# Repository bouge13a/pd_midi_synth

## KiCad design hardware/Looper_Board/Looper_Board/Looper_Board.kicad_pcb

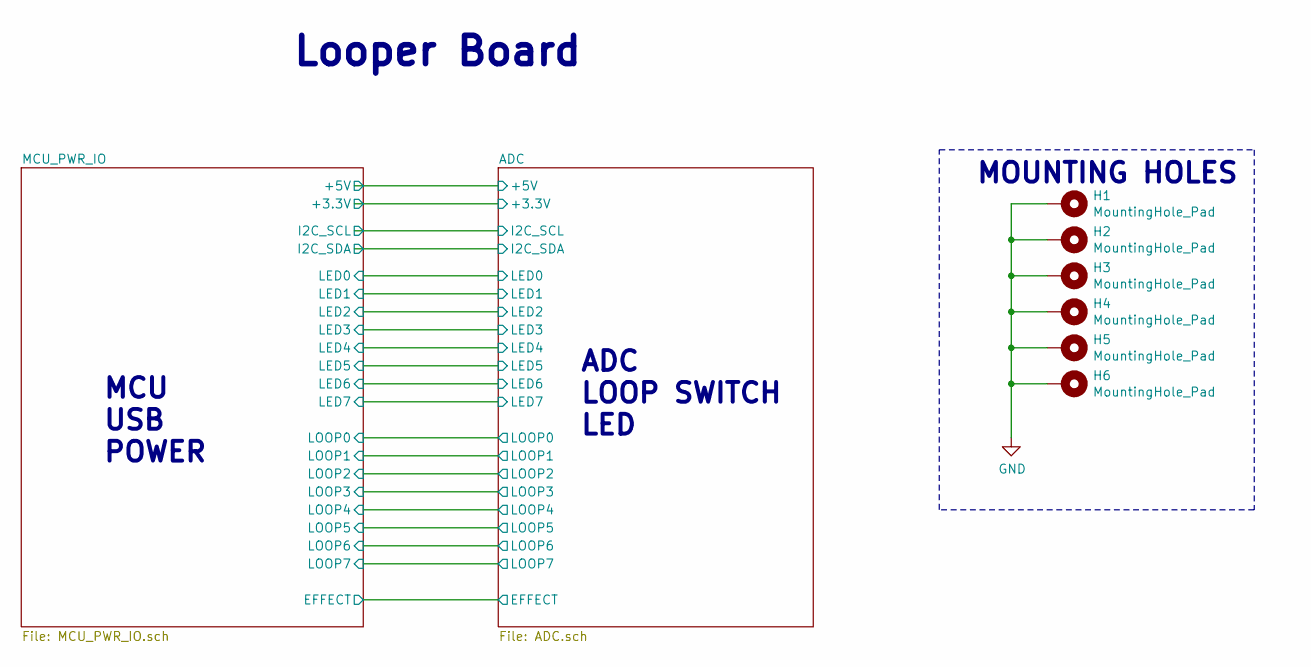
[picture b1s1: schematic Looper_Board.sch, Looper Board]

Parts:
H1, H2, H3, H4, H5, H6: MountingHole_Pad; MountingHole_3mm_Pad_Via

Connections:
GND: H1.1, H2.1, H3.1, H4.1, H5.1, H6.1; also elsewhere on the board

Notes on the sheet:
ADC LOOP SWITCH LED
MCU USB POWER
Looper Board
MOUNTING HOLES

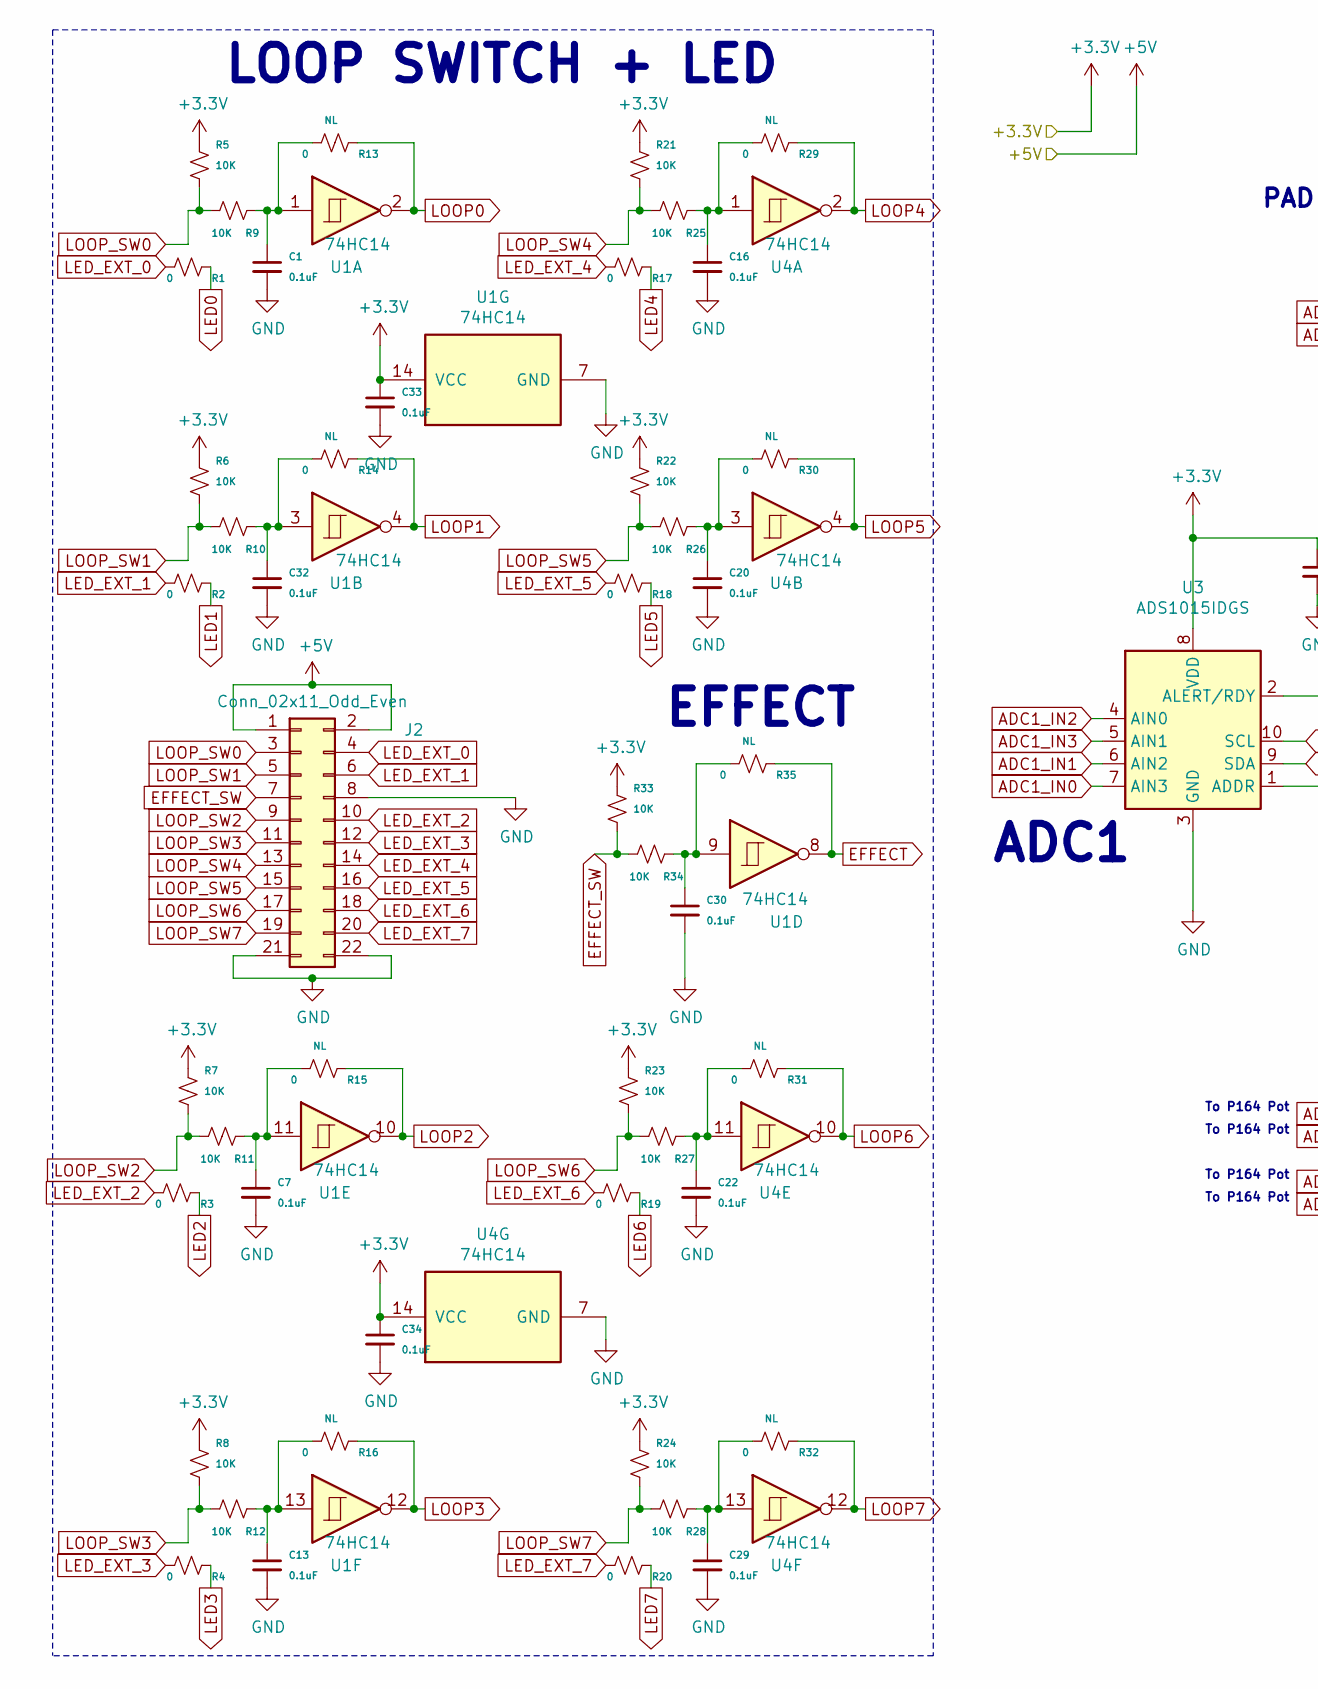
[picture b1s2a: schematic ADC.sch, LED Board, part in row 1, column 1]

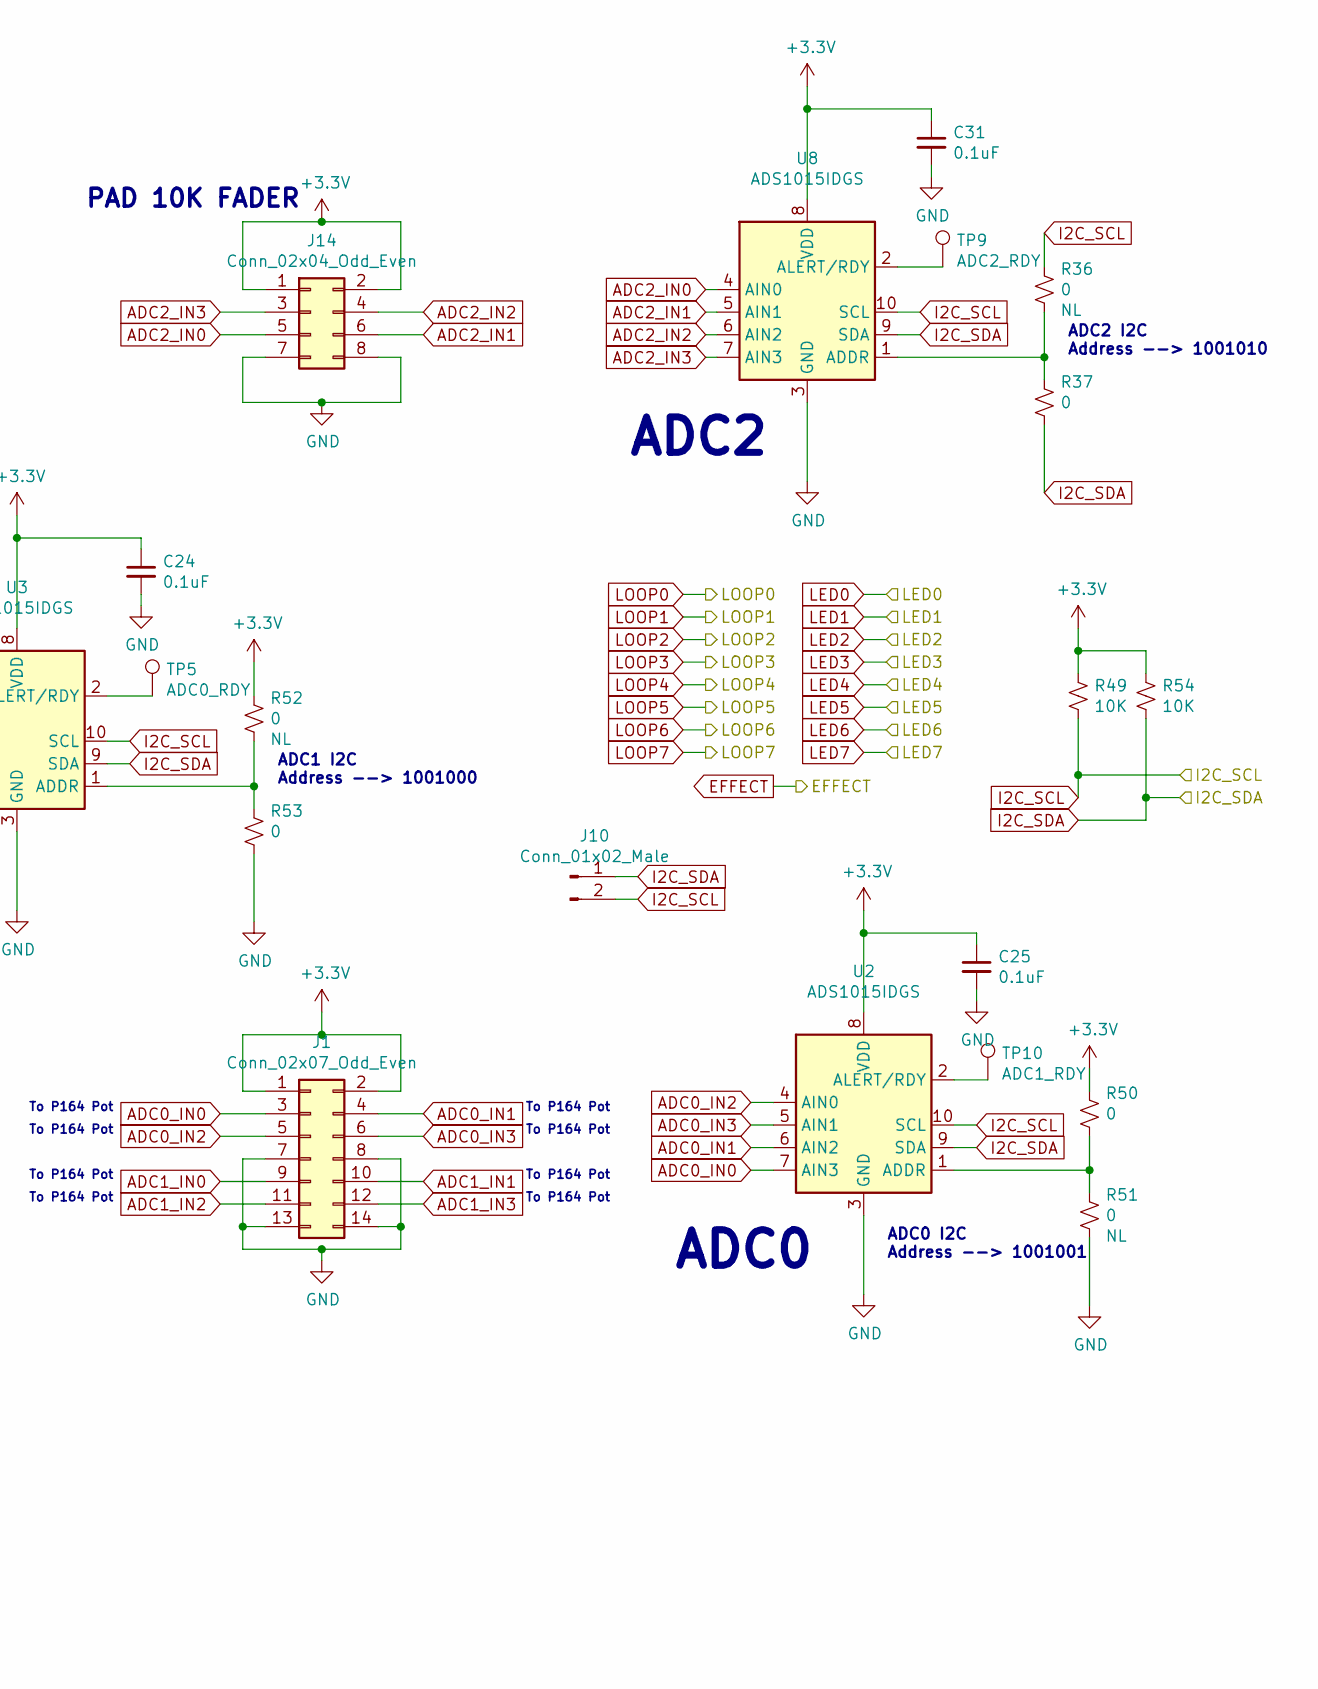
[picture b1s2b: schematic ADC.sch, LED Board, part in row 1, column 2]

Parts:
C1, C7, C13, C16, C20, C22, C24, C25, C29, C30, C31, C32, C33, C34: 0.1uF; C_0402_1005Metric_Pad0.74x0.62mm_HandSolder
J1: Conn_02x07_Odd_Even; PinHeader_2x07_P2.54mm_Horizontal
J2: Conn_02x11_Odd_Even; PinHeader_2x11_P2.54mm_Horizontal
J10: Conn_01x02_Male; PinHeader_1x02_P2.54mm_Vertical
J14: Conn_02x04_Odd_Even; PinHeader_2x04_P2.54mm_Horizontal
R1, R2, R3, R4, R13, R14, R15, R16, R17, R18, R19, R20, R29, R30, R31, R32, R35, R36, R37, R50, R51, R52, R53: 0; R_0402_1005Metric_Pad0.72x0.64mm_HandSolder
R5, R6, R7, R8, R9, R10, R11, R12, R21, R22, R23, R24, R25, R26, R27, R28, R33, R34, R49, R54: 10K; R_0402_1005Metric_Pad0.72x0.64mm_HandSolder
TP5: ADC0_RDY; TestPoint_Pad_D1.5mm
TP9: ADC2_RDY; TestPoint_Pad_D1.5mm
TP10: ADC1_RDY; TestPoint_Pad_D1.5mm
U1, U4: 74HC14; SOIC-14_3.9x8.7mm_P1.27mm
U2, U3, U8: ADS1015IDGS; VSSOP-10_3x3mm_P0.5mm

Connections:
+3V3: C24.1, C25.1, C31.1, C33.1, C34.1, J1.1, J1.2, J14.1, J14.2, R5.1, R6.1, R7.1, R8.1, R21.1, R22.1, R23.1, R24.1, R33.1, R49.1, R50.1, R52.1, R54.1, U1.14 (VCC), U2.8 (VDD), U3.8 (VDD), U4.14 (VCC), U8.8 (VDD); also elsewhere on the board
+5V: J2.1, J2.2; also elsewhere on the board
ADC0_IN0: J1.3, U2.7 (AIN3)
ADC0_IN1: J1.4, U2.6 (AIN2)
ADC0_IN2: J1.5, U2.4 (AIN0)
ADC0_IN3: J1.6, U2.5 (AIN1)
ADC1_IN0: J1.9, U3.7 (AIN3)
ADC1_IN1: J1.10, U3.6 (AIN2)
ADC1_IN2: J1.11, U3.4 (AIN0)
ADC1_IN3: J1.12, U3.5 (AIN1)
ADC2_IN0: J14.5, U8.4 (AIN0)
ADC2_IN1: J14.6, U8.5 (AIN1)
ADC2_IN2: J14.4, U8.6 (AIN2)
ADC2_IN3: J14.3, U8.7 (AIN3)
EFFECT: R35.1, U1.8; also elsewhere on the board
EFFECT_SW: J2.7, R33.2, R34.2
GND: C1.2, C7.2, C13.2, C16.2, C20.2, C22.2, C24.2, C25.2, C29.2, C30.2, C31.2, C32.2, C33.2, C34.2, J1.7, J1.8, J1.13, J1.14, J2.8, J2.21, J2.22, J14.7, J14.8, R51.2, R53.2, U1.7 (GND), U2.3 (GND), U3.3 (GND), U4.7 (GND), U8.3 (GND); also elsewhere on the board
I2C_SCL: J10.2, R36.1, R49.2, U2.10 (SCL), U3.10 (SCL), U8.10 (SCL); also elsewhere on the board
I2C_SDA: J10.1, R37.2, R54.2, U2.9 (SDA), U3.9 (SDA), U8.9 (SDA); also elsewhere on the board
LED0: R1.1; also elsewhere on the board
LED1: R2.1; also elsewhere on the board
LED2: R3.1; also elsewhere on the board
LED3: R4.1; also elsewhere on the board
LED4: R17.1; also elsewhere on the board
LED5: R18.1; also elsewhere on the board
LED6: R19.1; also elsewhere on the board
LED7: R20.1; also elsewhere on the board
LED_EXT_0: J2.4, R1.2
LED_EXT_1: J2.6, R2.2
LED_EXT_2: J2.10, R3.2
LED_EXT_3: J2.12, R4.2
LED_EXT_4: J2.14, R17.2
LED_EXT_5: J2.16, R18.2
LED_EXT_6: J2.18, R19.2
LED_EXT_7: J2.20, R20.2
LOOP0: R13.1, U1.2; also elsewhere on the board
LOOP1: R14.1, U1.4; also elsewhere on the board
LOOP2: R15.1, U1.10; also elsewhere on the board
LOOP3: R16.1, U1.12; also elsewhere on the board
LOOP4: R29.1, U4.2; also elsewhere on the board
LOOP5: R30.1, U4.4; also elsewhere on the board
LOOP6: R31.1, U4.10; also elsewhere on the board
LOOP7: R32.1, U4.12; also elsewhere on the board
LOOP_SW0: J2.3, R5.2, R9.2
LOOP_SW1: J2.5, R6.2, R10.2
LOOP_SW2: J2.9, R7.2, R11.2
LOOP_SW3: J2.11, R8.2, R12.2
LOOP_SW4: J2.13, R21.2, R25.2
LOOP_SW5: J2.15, R22.2, R26.2
LOOP_SW6: J2.17, R23.2, R27.2
LOOP_SW7: J2.19, R24.2, R28.2
unnamed: C1.1, R9.1, R13.2, U1.1
unnamed: C7.1, R11.1, R15.2, U1.11
unnamed: C13.1, R12.1, R16.2, U1.13
unnamed: C16.1, R25.1, R29.2, U4.1
unnamed: C20.1, R26.1, R30.2, U4.3
unnamed: C22.1, R27.1, R31.2, U4.11
unnamed: C29.1, R28.1, R32.2, U4.13
unnamed: C30.1, R34.1, R35.2, U1.9
unnamed: C32.1, R10.1, R14.2, U1.3
unnamed: R36.2, R37.1, U8.1 (ADDR)
unnamed: R50.2, R51.1, U2.1 (ADDR)
unnamed: R52.2, R53.1, U3.1 (ADDR)
unnamed: TP5.1, U3.2 (ALERT/RDY)
unnamed: TP9.1, U8.2 (ALERT/RDY)
unnamed: TP10.1, U2.2 (ALERT/RDY)

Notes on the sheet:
To P164 Pot
ADC0
ADC1
ADC1 I2C Address --> 1001000
ADC0 I2C Address --> 1001001
LOOP SWITCH + LED
EFFECT
ADC2
ADC2 I2C Address --> 1001010
PAD 10K FADER

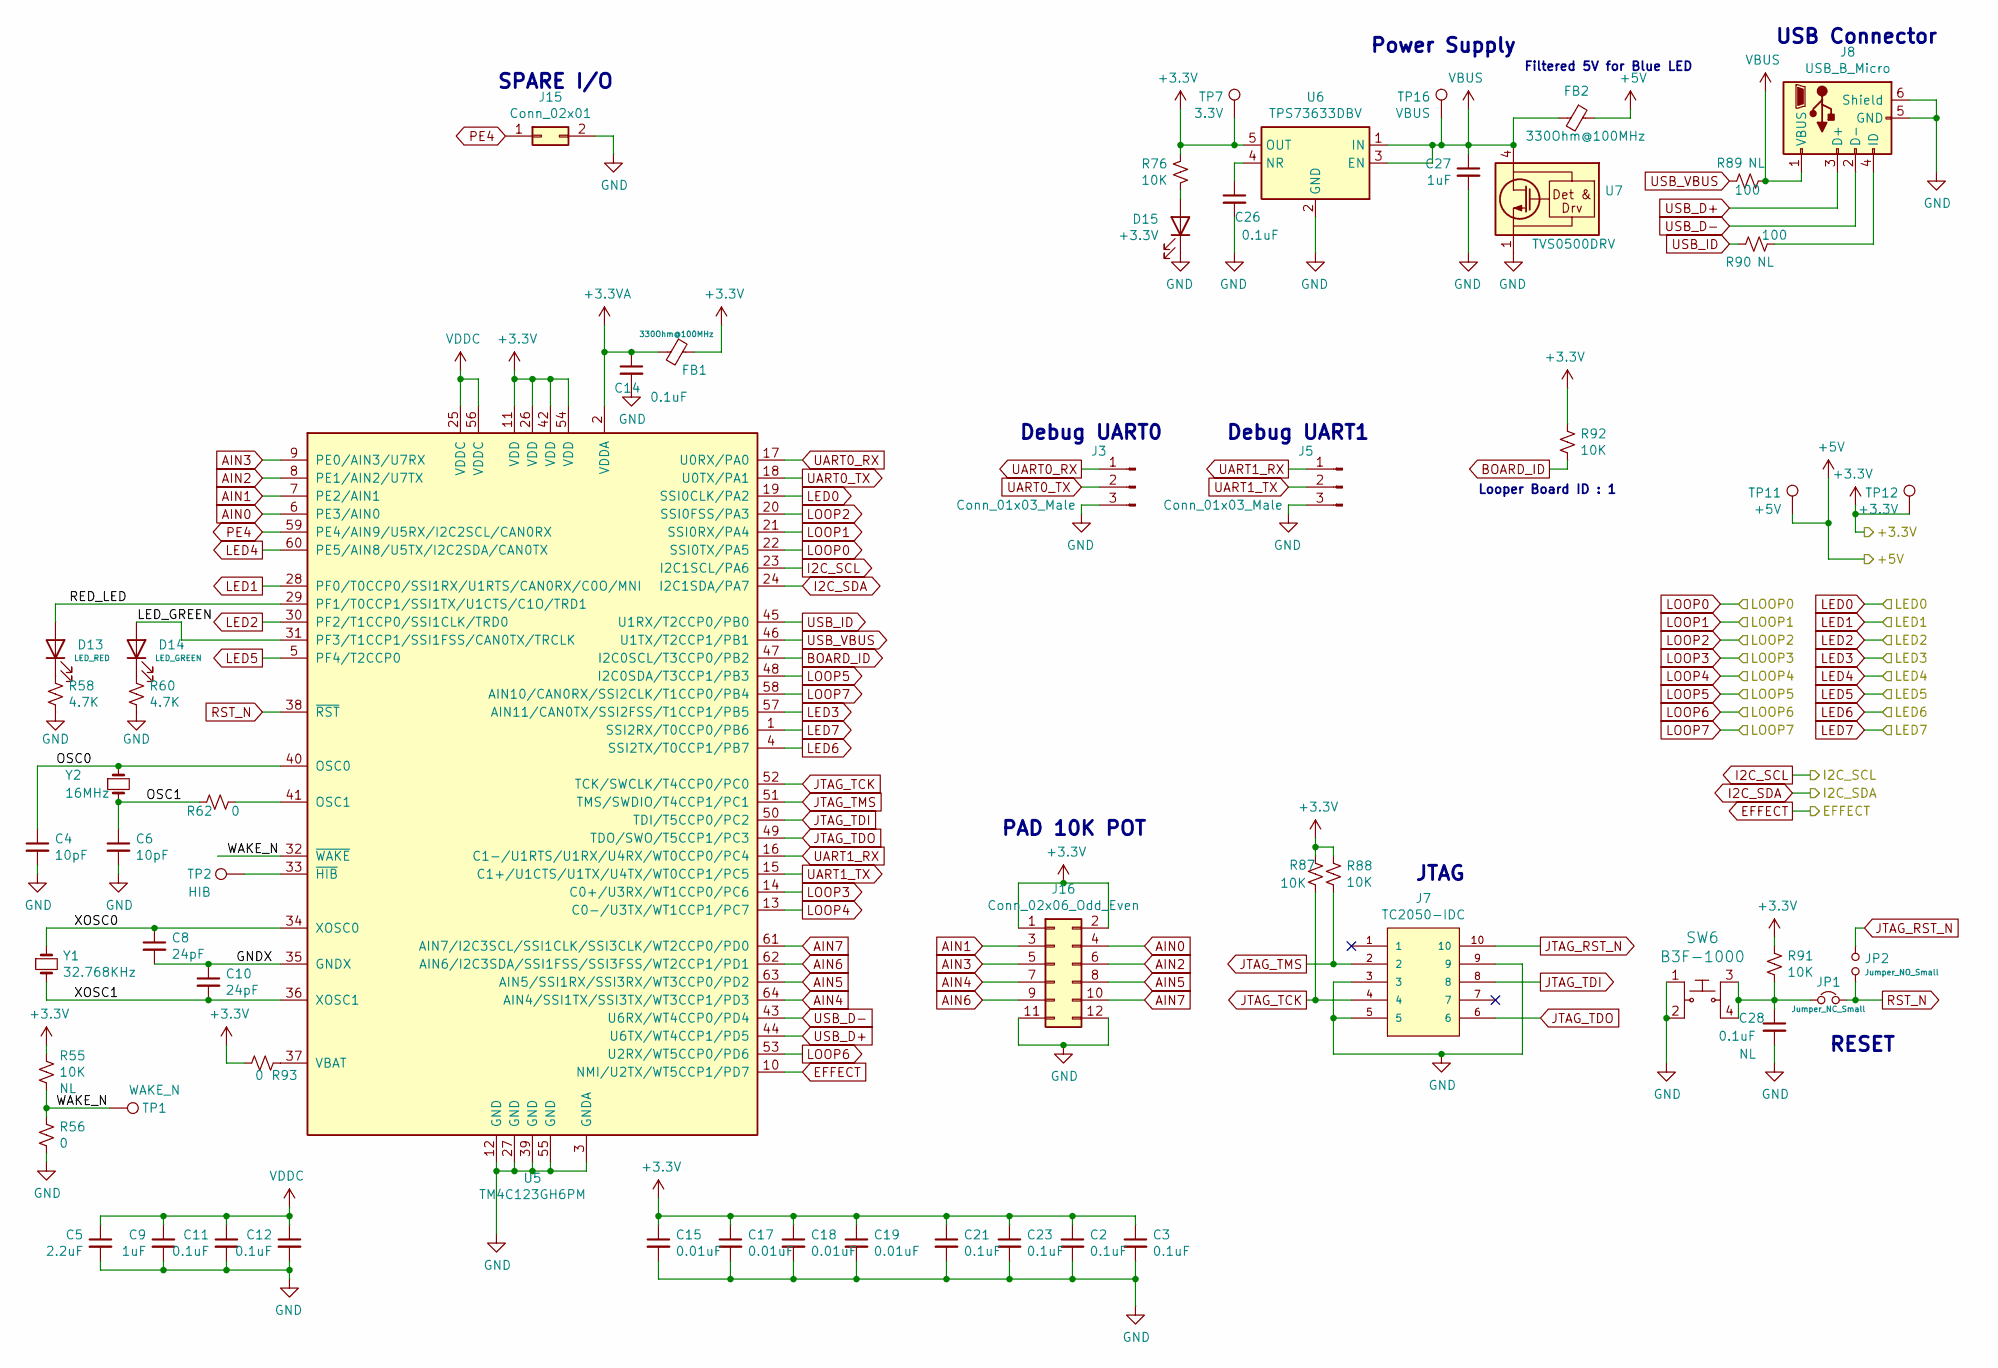
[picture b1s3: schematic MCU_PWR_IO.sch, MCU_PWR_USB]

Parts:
C2, C3, C11, C12, C14, C21, C23, C26, C28: 0.1uF; C_0402_1005Metric_Pad0.74x0.62mm_HandSolder
C4, C6: 10pF; C_0402_1005Metric_Pad0.74x0.62mm_HandSolder
C5: 2.2uF; C_0603_1608Metric_Pad1.08x0.95mm_HandSolder
C8, C10: 24pF; C_0402_1005Metric_Pad0.74x0.62mm_HandSolder
C9, C27: 1uF; C_0402_1005Metric_Pad0.74x0.62mm_HandSolder
C15, C17, C18, C19: 0.01uF; C_0402_1005Metric_Pad0.74x0.62mm_HandSolder
D13: LED_RED; LED_0603_1608Metric
D14: LED_GREEN; LED_0603_1608Metric
D15: +3.3V; LED_0603_1608Metric
FB1: 330Ohm@100MHz; L_0805_2012Metric_Pad1.15x1.40mm_HandSolder; MfrPart GZ2012D601TF
FB2: 330Ohm@100MHz; L_0805_2012Metric_Pad1.15x1.40mm_HandSolder; MfrPart BLM18BB331SN1D
J3, J5: Conn_01x03_Male; PinHeader_1x03_P2.54mm_Vertical
J7: TC2050-IDC; TAG-CONNECT_TC2050-IDC; PARTREV A
J8: USB_B_Micro; USB_Micro-AB_Molex_47590-0001
J15: Conn_02x01; PinHeader_2x01_P2.54mm_Vertical
J16: Conn_02x06_Odd_Even; PinHeader_2x06_P2.54mm_Horizontal
JP1: Jumper_NC_Small; PinHeader_1x02_P2.54mm_Vertical
JP2: Jumper_NO_Small; PinHeader_1x02_P2.54mm_Vertical
R55, R76, R87, R88, R91, R92: 10K; R_0402_1005Metric_Pad0.72x0.64mm_HandSolder
R56, R62, R93: 0; R_0402_1005Metric_Pad0.72x0.64mm_HandSolder
R58, R60: 4.7K; R_0402_1005Metric_Pad0.72x0.64mm_HandSolder
R89, R90: 100; R_0402_1005Metric_Pad0.72x0.64mm_HandSolder
SW6: B3F-1000; SW_SPST_Omron_B3FS-100xP; MPN B3F-1000; Digi-Key_PN SW400-ND
TP1: WAKE_N; TestPoint_Pad_D1.5mm
TP2: HIB; TestPoint_Pad_D1.5mm
TP7: 3.3V; TestPoint_Pad_D1.5mm
TP11: +5V; TestPoint_Pad_D1.5mm
TP12: +3.3V; TestPoint_Pad_D1.5mm
TP16: VBUS; TestPoint_Pad_D1.5mm
U5: TM4C123GH6PM; LQFP-64_10x10mm_P0.5mm
U6: TPS73633DBV; SOT-23-5
U7: TVS0500DRV; WSON-6-1EP_2x2mm_P0.65mm_EP1x1.6mm
Y1: 32.768KHz; XTAL_AB26TRB-32.768KHZ-T
Y2: 16MHz; CRYSTAL_5_3.2MM

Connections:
+3.3VA: C14.1, FB1.2, U5.2 (VDDA)
+3V3: C2.1, C3.1, C15.1, C17.1, C18.1, C19.1, C21.1, C23.1, FB1.1, J16.1, J16.2, R55.1, R76.1, R87.1, R88.1, R91.1, R92.1, R93.2, TP7.1, TP12.1, U5.11 (VDD), U5.26 (VDD), U5.42 (VDD), U5.54 (VDD), U6.5 (OUT); also elsewhere on the board
+5V: FB2.1, TP11.1; also elsewhere on the board
/MCU_PWR_IO/GNDX: C8.2, C10.1, U5.35 (GNDX)
/MCU_PWR_IO/LED_GREEN: D14.2 (A), U5.31 (PF3/T1CCP1/SSI1FSS/CAN0TX/TRCLK)
/MCU_PWR_IO/OSC0: C4.1, U5.40 (OSC0), Y2.1
/MCU_PWR_IO/OSC1: C6.1, R62.2, Y2.2
/MCU_PWR_IO/RED_LED: D13.2 (A), U5.29 (PF1/T0CCP1/SSI1TX/U1CTS/C1O/TRD1)
/MCU_PWR_IO/WAKE_N: R55.2, R56.1, TP1.1, U5.32 (~WAKE~)
/MCU_PWR_IO/XOSC0: C8.1, U5.34 (XOSC0), Y1.1
/MCU_PWR_IO/XOSC1: C10.2, U5.36 (XOSC1), Y1.2
AIN0: J16.4, U5.6 (PE3/AIN0)
AIN1: J16.3, U5.7 (PE2/AIN1)
AIN2: J16.6, U5.8 (PE1/AIN2/U7TX)
AIN3: J16.5, U5.9 (PE0/AIN3/U7RX)
AIN4: J16.7, U5.64 (AIN4/SSI1TX/SSI3TX/WT3CCP1/PD3)
AIN5: J16.8, U5.63 (AIN5/SSI1RX/SSI3RX/WT3CCP0/PD2)
AIN6: J16.9, U5.62 (AIN6/I2C3SDA/SSI1FSS/SSI3FSS/WT2CCP1/PD1)
AIN7: J16.10, U5.61 (AIN7/I2C3SCL/SSI1CLK/SSI3CLK/WT2CCP0/PD0)
BOARD_ID: R92.2, U5.47 (I2C0SCL/T3CCP0/PB2)
EFFECT: U5.10 (NMI/U2TX/WT5CCP1/PD7); also elsewhere on the board
GND: C2.2, C3.2, C4.2, C5.2, C6.2, C9.2, C11.2, C12.2, C14.2, C15.2, C17.2, C18.2, C19.2, C21.2, C23.2, C26.2, C27.2, C28.2, D15.1 (K), J3.3, J5.3, J7.3, J7.5, J7.9, J8.5 (GND), J8.6 (Shield), J15.2, J16.11, J16.12, R56.2, R58.2, R60.2, SW6.1, SW6.2, U5.3 (GNDA), U5.12 (GND), U5.27 (GND), U5.39 (GND), U5.55 (GND), U6.2 (GND), U7.1 (GND), U7.2 (GND), U7.3 (GND), U7.7 (GND); also elsewhere on the board
I2C_SCL: U5.23 (I2C1SCL/PA6); also elsewhere on the board
I2C_SDA: U5.24 (I2C1SDA/PA7); also elsewhere on the board
JTAG_RST_N: J7.10, JP2.1
JTAG_TCK: J7.4, R87.2, U5.52 (TCK/SWCLK/T4CCP0/PC0)
JTAG_TDI: J7.8, U5.50 (TDI/T5CCP0/PC2)
JTAG_TDO: J7.6, U5.49 (TDO/SWO/T5CCP1/PC3)
JTAG_TMS: J7.2, R88.2, U5.51 (TMS/SWDIO/T4CCP1/PC1)
LED0: U5.19 (SSI0CLK/PA2); also elsewhere on the board
LED1: U5.28 (PF0/T0CCP0/SSI1RX/U1RTS/CAN0RX/C0O/MNI); also elsewhere on the board
LED2: U5.30 (PF2/T1CCP0/SSI1CLK/TRD0); also elsewhere on the board
LED3: U5.57 (AIN11/CAN0TX/SSI2FSS/T1CCP1/PB5); also elsewhere on the board
LED4: U5.60 (PE5/AIN8/U5TX/I2C2SDA/CAN0TX); also elsewhere on the board
LED5: U5.5 (PF4/T2CCP0); also elsewhere on the board
LED6: U5.4 (SSI2TX/T0CCP1/PB7); also elsewhere on the board
LED7: U5.1 (SSI2RX/T0CCP0/PB6); also elsewhere on the board
LOOP0: U5.22 (SSI0TX/PA5); also elsewhere on the board
LOOP1: U5.21 (SSI0RX/PA4); also elsewhere on the board
LOOP2: U5.20 (SSI0FSS/PA3); also elsewhere on the board
LOOP3: U5.14 (C0+/U3RX/WT1CCP0/PC6); also elsewhere on the board
LOOP4: U5.13 (C0-/U3TX/WT1CCP1/PC7); also elsewhere on the board
LOOP5: U5.48 (I2C0SDA/T3CCP1/PB3); also elsewhere on the board
LOOP6: U5.53 (U2RX/WT5CCP0/PD6); also elsewhere on the board
LOOP7: U5.58 (AIN10/CAN0RX/SSI2CLK/T1CCP0/PB4); also elsewhere on the board
unnamed: C26.1, U6.4 (NR)
unnamed: C28.1, JP1.1, R91.2, SW6.3, SW6.4
unnamed: D13.1 (K), R58.1
unnamed: D14.1 (K), R60.1
unnamed: D15.2 (A), R76.2
unnamed: J8.4 (ID), R90.1
unnamed: R62.1, U5.41 (OSC1)
unnamed: R93.1, U5.37 (VBAT)
unnamed: TP2.1, U5.33 (~HIB~)
PE4: J15.1, U5.59 (PE4/AIN9/U5RX/I2C2SCL/CAN0RX)
RST_N: JP1.2, JP2.2, U5.38 (~RST~)
UART0_RX: J3.1, U5.17 (U0RX/PA0)
UART0_TX: J3.2, U5.18 (U0TX/PA1)
UART1_RX: J5.1, U5.16 (C1-/U1RTS/U1RX/U4RX/WT0CCP0/PC4)
UART1_TX: J5.2, U5.15 (C1+/U1CTS/U1TX/U4TX/WT0CCP1/PC5)
USB_D+: J8.3 (D+), U5.44 (U6TX/WT4CCP1/PD5)
USB_D-: J8.2 (D-), U5.43 (U6RX/WT4CCP0/PD4)
USB_ID: R90.2, U5.45 (U1RX/T2CCP0/PB0)
USB_VBUS: R89.2, U5.46 (U1TX/T2CCP1/PB1)
VBUS: C27.1, FB2.2, J8.1 (VBUS), R89.1, TP16.1, U6.1 (IN), U6.3 (EN), U7.4 (IN), U7.5 (IN), U7.6 (IN)
VDDC: C5.1, C9.1, C11.1, C12.1, U5.25 (VDDC), U5.56 (VDDC)

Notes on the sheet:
Filtered 5V for Blue LED
JTAG
Power Supply
USB Connector
RESET
Looper Board ID : 1
Debug UART0
Debug UART1
PAD 10K POT
SPARE I/O

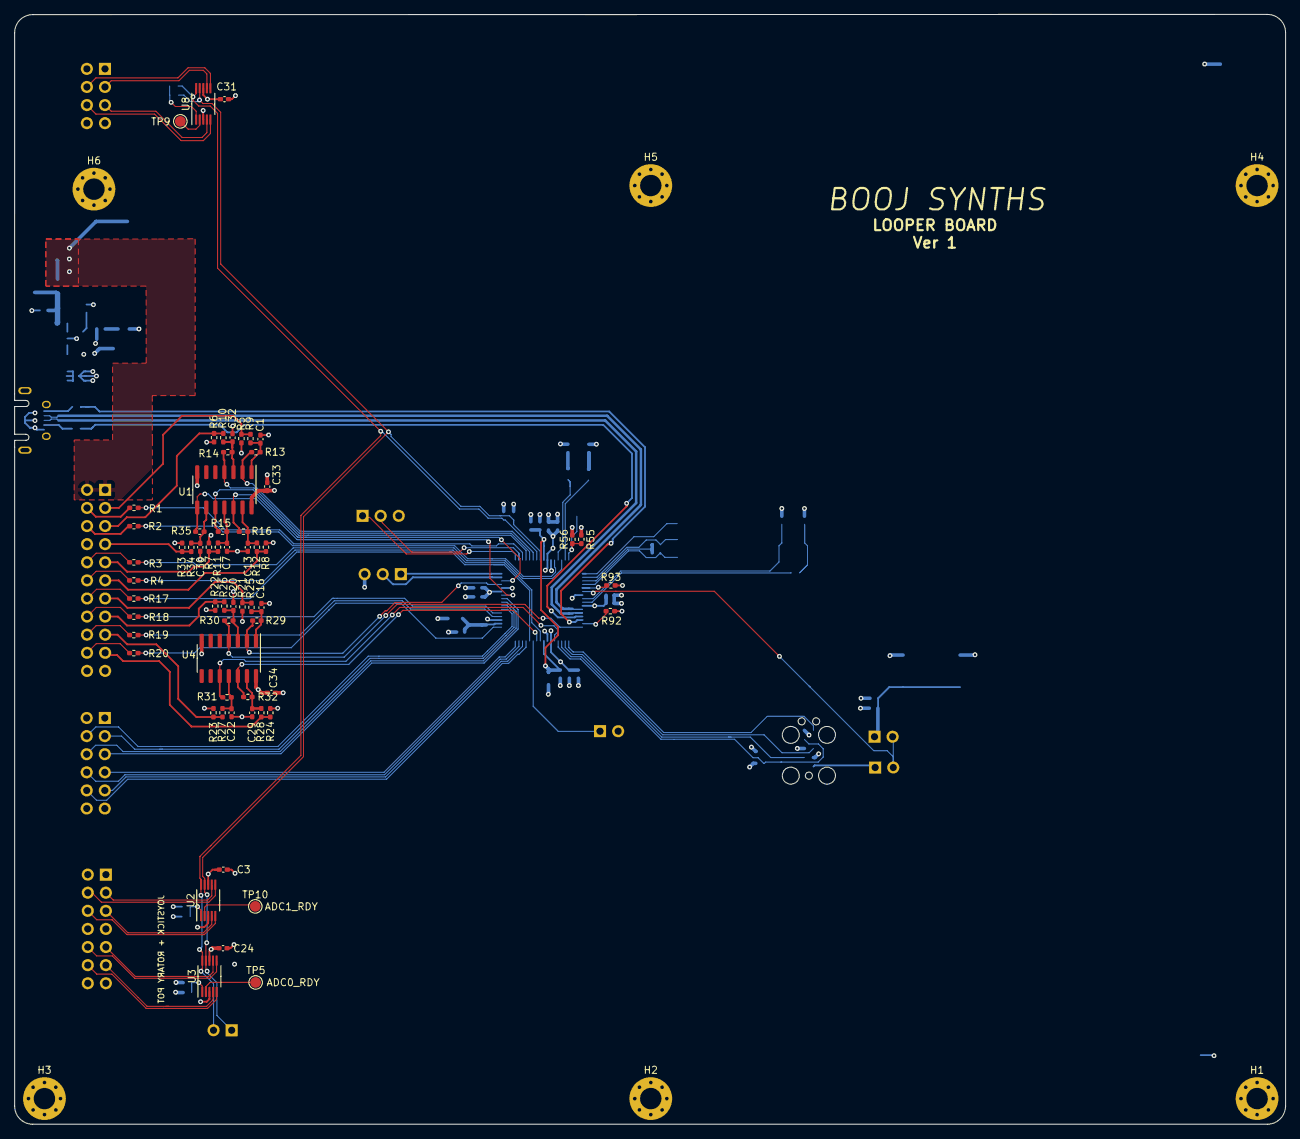
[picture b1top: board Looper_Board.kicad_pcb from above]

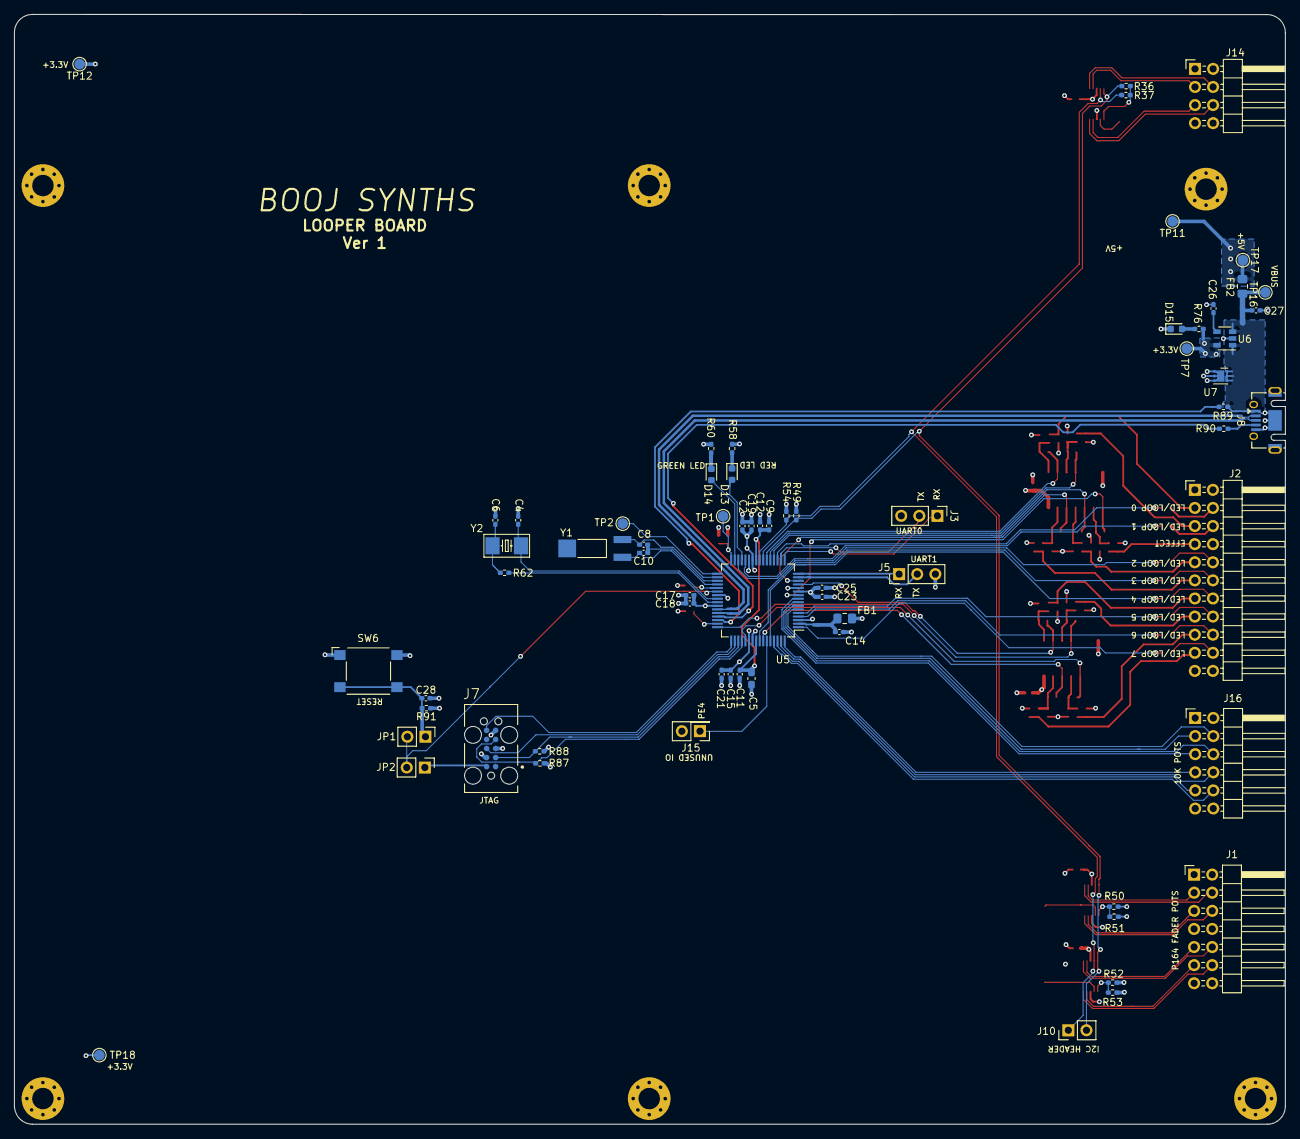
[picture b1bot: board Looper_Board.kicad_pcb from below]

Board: 4 copper layers, 178.3 x 155.7 mm, 135 parts (68 on the bottom side), 110 nets.

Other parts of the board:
TP17: +5V; TestPoint_Pad_D1.5mm
TP18: +3.3V; TestPoint_Pad_D1.5mm

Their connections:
+3V3: TP18.1; also elsewhere on the board
+5V: TP17.1; also elsewhere on the board

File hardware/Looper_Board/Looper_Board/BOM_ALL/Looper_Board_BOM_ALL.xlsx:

Comment | Designator | Footprint | LCSC | Components from Digikey
0.01uF | C15,C17,C18,C19 | Capacitor_SMD:C_0402_1005Metric_Pad0.74x0.62mm_HandSolder | C15195
0.1uF | C1,C2,C3,C7,C11,C12,C13,C14,C16,C20,C21,C22,C23,C24,C25,C26,C28,C29,C30,C31,C32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 | Capacitor_SMD:C_0402_1005Metric_Pad0.74x0.62mm_HandSolder | C1525
10pF | C4,C6 | Capacitor_SMD:C_0402_1005Metric_Pad0.74x0.62mm_HandSolder | C32949
2.2uF | C5 | Capacitor_SMD:C_0603_1608Metric_Pad1.08x0.95mm_HandSolder | C57895
24pF | C8,C10 | Capacitor_SMD:C_0402_1005Metric_Pad0.74x0.62mm_HandSolder | C22728
1uF | C9,C27 | Capacitor_SMD:C_0402_1005Metric_Pad0.74x0.62mm_HandSolder | C28323
LED_RED | D13 | LED_SMD:LED_0603_1608Metric | C72044
LED_GREEN | D14 | LED_SMD:LED_0603_1608Metric | C72043
+3.3V | D15 | LED_SMD:LED_0603_1608Metric | C72043
330Ohm@100MHz | FB1,FB2 | Inductor_SMD:L_0805_2012Metric_Pad1.15x1.40mm_HandSolder | C1017
Conn_02x07_Odd_Even | J1 | Connector_PinHeader_2.54mm:PinHeader_2x07_P2.54mm_Horizontal |  | HTSS-114-04-G-D-RA
Conn_02x04_Odd_Even | J14 | Connector_PinHeader_2.54mm:PinHeader_2x04_P2.54mm_Horizontal |  | TSW-104-23-G-D
Conn_01x02_Male | J10 | Connector_PinHeader_2.54mm:PinHeader_1x02_P2.54mm_Vertical | C160332
Conn_02x01 | J15 | Connector_PinHeader_2.54mm:PinHeader_2x01_P2.54mm_Vertical | C160332
Conn_02x06_Odd_Even | J16 | Connector_PinHeader_2.54mm:PinHeader_2x06_P2.54mm_Horizontal |  | HTSS-106-04-G-D-RA
Conn_02x11_Odd_Even | J2 | Connector_PinHeader_2.54mm:PinHeader_2x11_P2.54mm_Horizontal |  | 78207-122HLF
Conn_01x03_Male | J3,J5 | Connector_PinHeader_2.54mm:PinHeader_1x03_P2.54mm_Vertical | C306138
TC2050-IDC | J7 | TC2050-IDC:TAG-CONNECT_TC2050-IDC
USB_B_Micro | J8 | Connector_USB:USB_Micro-AB_Molex_47590-0001 | C145779
Jumper_NC_Small | JP1 | Connector_PinHeader_2.54mm:PinHeader_1x02_P2.54mm_Vertical | C160332
Jumper_NO_Small | JP2 | Connector_PinHeader_2.54mm:PinHeader_1x02_P2.54mm_Vertical | C160332
0 | R1,R2,R3,R4,R13,R14,R15,R16,R17,R18,R19,R20,R29,R30,R31,R32,R35,R36,R37,R50,R51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 | Resistor_SMD:R_0402_1005Metric_Pad0.72x0.64mm_HandSolder | C17168
10K | R5,R6,R7,R8,R9,R10,R11,R12,R21,R22,R23,R24,R25,R26,R27,R28,R33,R34,R49,R54,R55,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 | Resistor_SMD:R_0402_1005Metric_Pad0.72x0.64mm_HandSolder | C25744
4.7K | R58,R60 | Resistor_SMD:R_0402_1005Metric_Pad0.72x0.64mm_HandSolder | C25900
100 | R89,R90 | Resistor_SMD:R_0402_1005Metric_Pad0.72x0.64mm_HandSolder | C25076
B3F-1000 | SW6 | Button_Switch_SMD:SW_SPST_Omron_B3FS-100xP | C271750
74HC14 | U1,U4 | Package_SO:SOIC-14_3.9x8.7mm_P1.27mm | C130461
ADS1015IDGS | U2,U3,U8 | Package_SO:VSSOP-10_3x3mm_P0.5mm | C193969
TM4C123GH6PM | U5 | Package_QFP:LQFP-64_10x10mm_P0.5mm | C544750
TPS73633DBV | U6 | Package_TO_SOT_SMD:SOT-23-5 | C28038
TVS0500DRV | U7 | Package_SON:WSON-6-1EP_2x2mm_P0.65mm_EP1x1.6mm |  | TVS0500DRVR
32.768KHz | Y1 | AB26TRB-32:XTAL_AB26TRB-32.768KHZ-T |  | AB26TRB-32.768KHZ-T
16MHz | Y2 | NX5032GA-16MHZ:CRYSTAL_5_3.2MM |  | NX5032GA-16MHZ-STD-CSK-4
